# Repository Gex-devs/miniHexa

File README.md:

# Mini Hexa

Rework of Hiwonders mini hexa 

# Version 2.0 

<!-- SCHEMA STARTS HERE -->

<!-- SCHEMA ENDS HERE -->

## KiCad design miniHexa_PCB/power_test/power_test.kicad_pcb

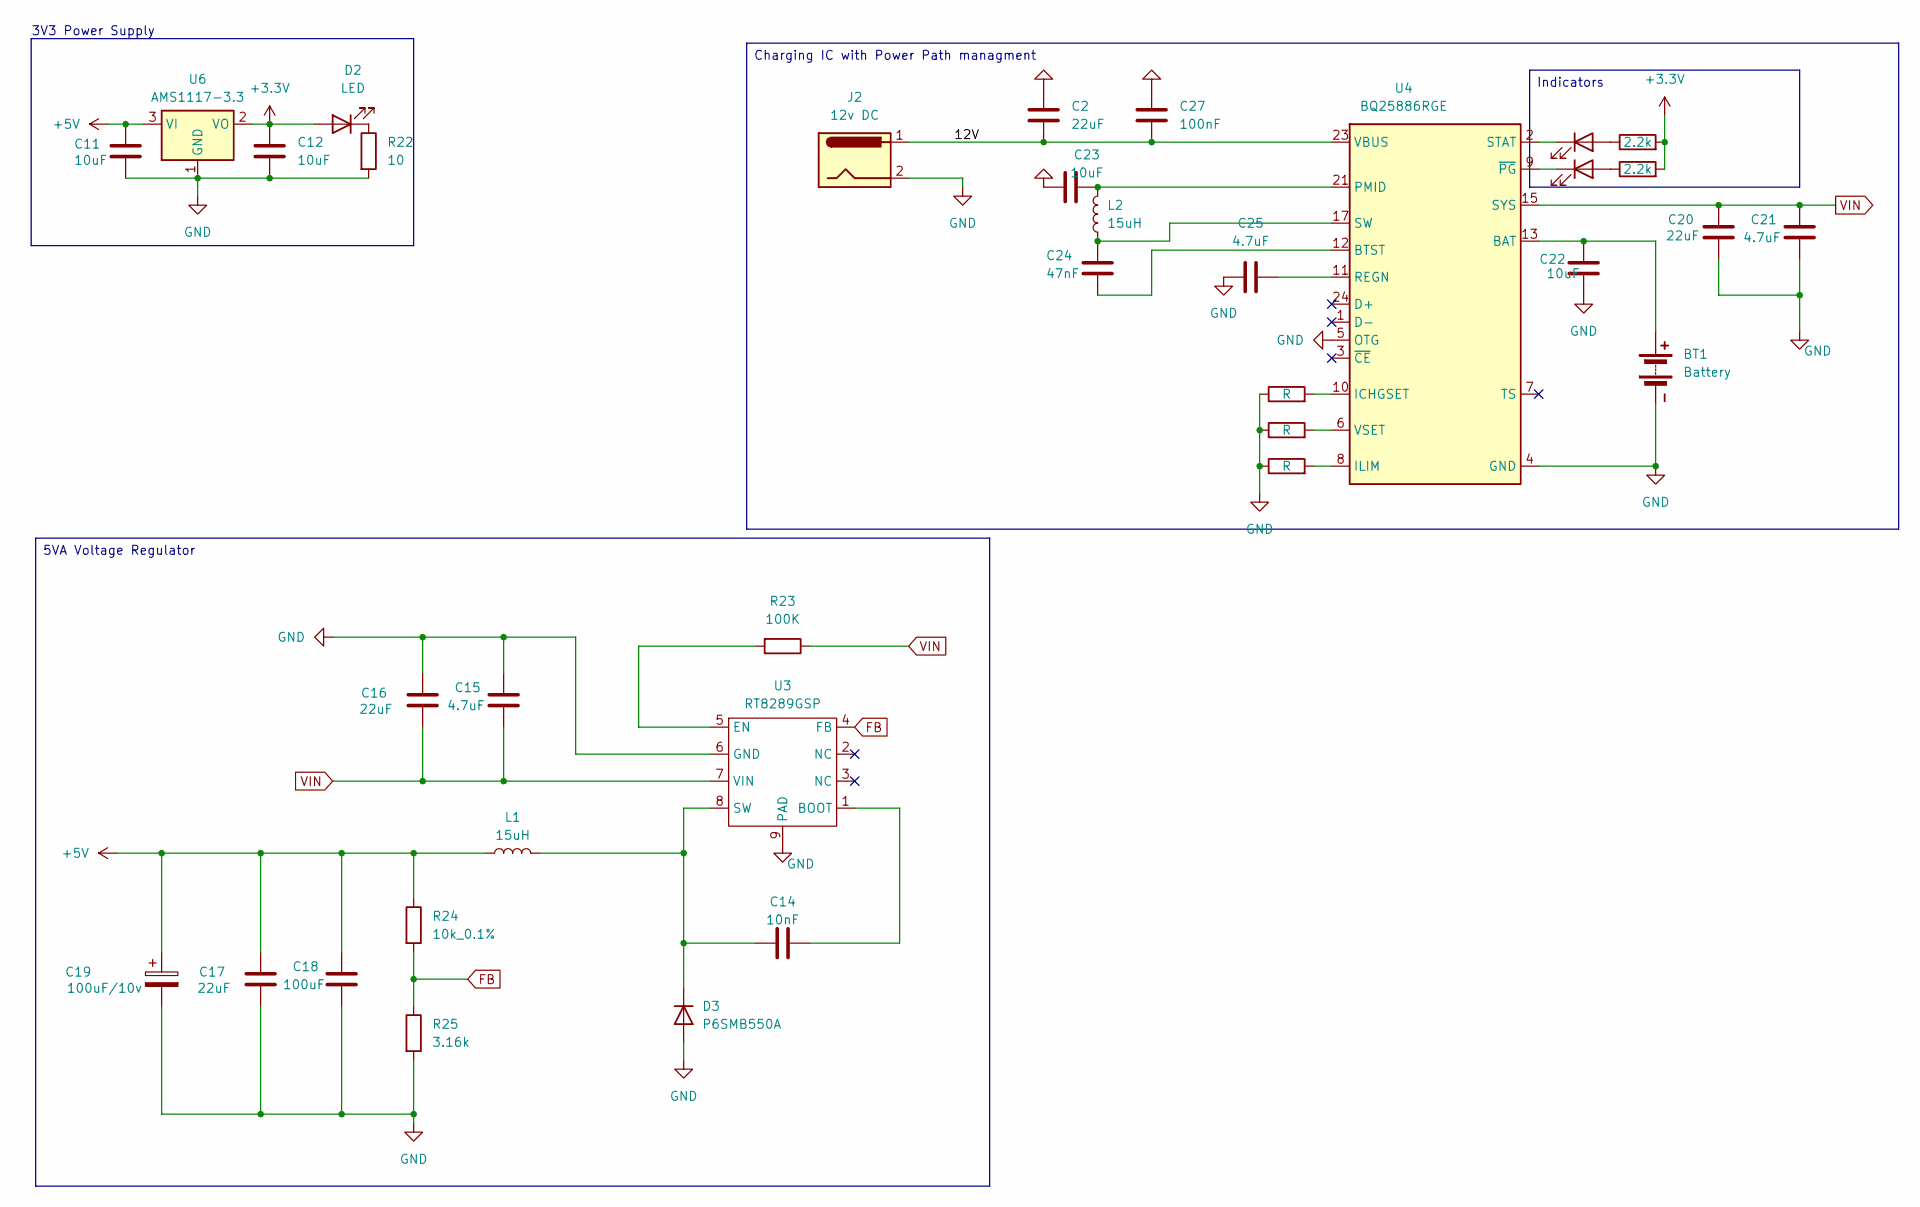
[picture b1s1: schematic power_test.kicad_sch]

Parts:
BT1: Battery; JST_XH_S2B-XH-A-1_1x02_P2.50mm_Horizontal
C2, C16, C17, C20: 22uF; C_0402_1005Metric
C11, C12, C22, C23: 10uF; C_0402_1005Metric
C14: 10nF; C_0402_1005Metric
C15, C21, C25: 4.7uF; C_0402_1005Metric
C18: 100uF; C_0402_1005Metric
C19: 100uF/10v; CP_Elec_5x5.4
C24: 47nF; C_0402_1005Metric
C27: 100nF; C_0402_1005Metric
D2, D4, D5: LED; LED_0805_2012Metric
D3: P6SMB550A; D_0805_2012Metric_Pad1.15x1.40mm_HandSolder
J2: 12v DC; BarrelJack_Wuerth_694102107102_1.0x3.9mm
L1, L2: 15uH; L_Panasonic_PCC-M0850M
R22: 10; R_0402_1005Metric
R23: 100K; R_0402_1005Metric
R24: 10k_0.1%; R_0402_1005Metric
R25: 3.16k; R_0402_1005Metric
R26, R30, R31: R; R_0402_1005Metric
R27, R28: 2.2k; R_0402_1005Metric
U3: RT8289GSP
U4: BQ25886RGE; Texas_RGE0024H_VQFN-24-1EP_4x4mm_P0.5mm_EP2.7x2.7mm
U6: AMS1117-3.3; SOT-223-3_TabPin2

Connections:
+3.3V: C12.1, D2.2 (A), R27.2, R28.2, U6.2 (VO)
+5V: C11.1, C17.2, C18.2, C19.1, L1.1, R24.1, U6.3 (VI)
/12V: C2.2, C27.2, J2.1, U4.23 (VBUS)
FB: R24.2, R25.1, U3.4 (FB)
GND: BT1.2 (GND), C2.1, C11.2, C12.2, C15.2, C16.2, C17.1, C18.1, C19.2, C20.1, C21.1, C22.2, C23.1, C25.1, C27.1, D3.2 (A), J2.2, R22.2, R25.2, R26.1, R30.1, R31.1, U3.6 (GND), U3.9 (PAD), U4.4 (GND), U4.5 (OTG), U4.19 (GND), U4.20 (GND), U4.25 (GND), U6.1 (GND)
unnamed: BT1.1 (+), C22.1, U4.13 (BAT), U4.14 (BAT)
unnamed: C23.2, L2.2, U4.21 (PMID), U4.22 (PMID)
unnamed: C24.1, L2.1, U4.17 (SW), U4.18 (SW)
unnamed: D2.1 (K), R22.1
unnamed: C14.1, D3.1 (K), L1.2, U3.8 (SW)
unnamed: D4.2 (A), R27.1
unnamed: D4.1 (K), U4.2 (STAT)
unnamed: D5.2 (A), R28.1
unnamed: D5.1 (K), U4.9 (~PG)
unnamed: C14.2, U3.1 (BOOT)
unnamed: R23.2, U3.5 (EN)
unnamed: C24.2, U4.12 (BTST)
unnamed: R26.2, U4.10 (ICHGSET)
unnamed: R31.2, U4.8 (ILIM)
unnamed: C25.2, U4.11 (REGN)
unnamed: R30.2, U4.6 (VSET)
VIN: C15.1, C16.1, C20.2, C21.2, R23.1, U3.7 (VIN), U4.15 (SYS), U4.16 (SYS)

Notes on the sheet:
3V3 Power Supply
5VA Voltage Regulator
Charging IC with Power Path managment
Indicators

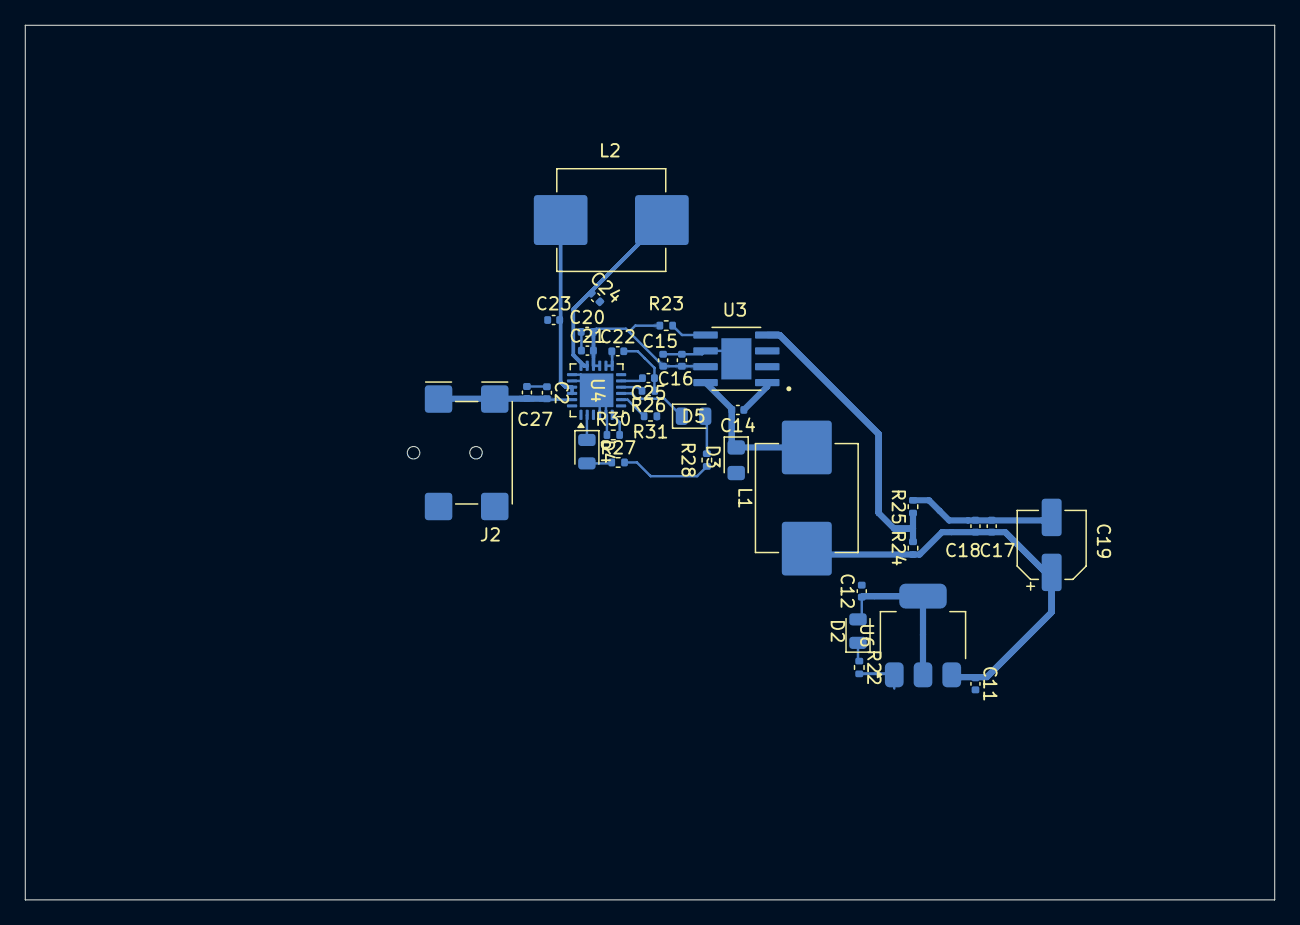
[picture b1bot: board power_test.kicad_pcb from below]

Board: 4 copper layers, 100.0 x 70.0 mm, 35 parts (35 on the bottom side), 22 nets.

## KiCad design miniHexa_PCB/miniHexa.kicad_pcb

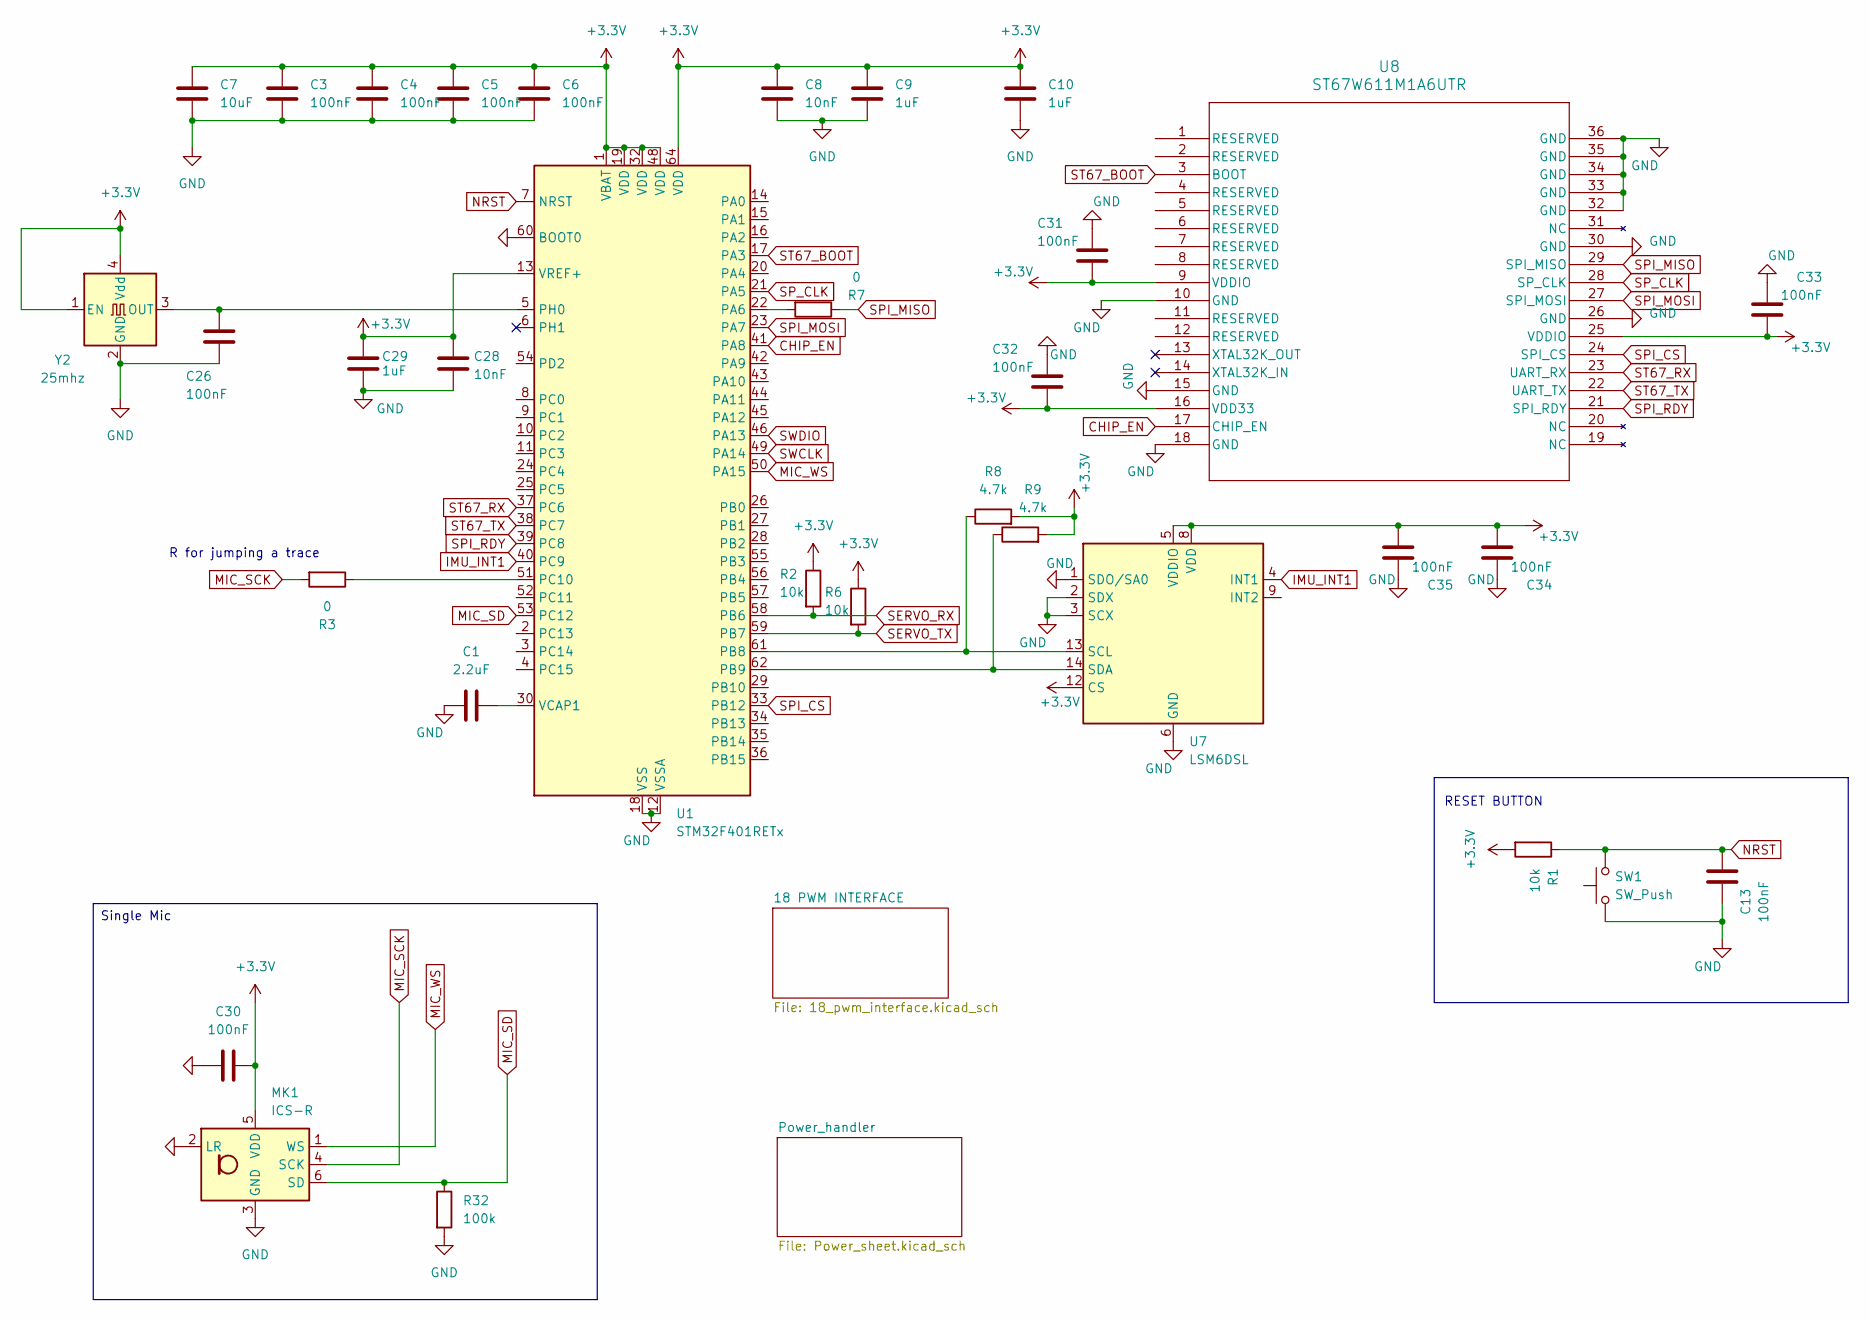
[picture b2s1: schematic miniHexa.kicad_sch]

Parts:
C1: 2.2uF; C_0402_1005Metric
C3, C4, C5, C6, C13, C26, C34, C35: 100nF; C_0402_1005Metric
C7: 10uF; C_0402_1005Metric
C8, C28: 10nF; C_0402_1005Metric
C9, C10, C29: 1uF; C_0402_1005Metric
C30, C31, C32, C33: 100nF; C_0805_2012Metric
MK1: ICS-R; InvenSense_ICS-43434-6_3.5x2.65mm
R1, R2, R6: 10k; R_0402_1005Metric
R3, R7: 0; R_0603_1608Metric
R8, R9: 4.7k; R_0402_1005Metric
R32: 100k; R_0402_1005Metric
SW1: SW_Push; SW_SPST_B3U-1000P
U1: STM32F401RETx; LQFP-64_10x10mm_P0.5mm
U7: LSM6DSL; LGA-14_3x2.5mm_P0.5mm_LayoutBorder3x4y
U8: ST67W611M1A6UTR; U_QFN32L_ST67W611M1_STM-L
Y2: 25mhz; Oscillator_SMD_Abracon_ASE-4Pin_3.2x2.5mm

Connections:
+3.3V: C3.1, C4.1, C5.1, C6.1, C7.1, C8.1, C9.1, C10.1, C28.1, C29.1, C30.2, C31.2, C32.2, C33.2, C34.2, C35.2, MK1.5 (VDD), R1.2, R2.1, R6.1, R8.2, R9.2, U1.1 (VBAT), U1.13 (VREF+), U1.19 (VDD), U1.32 (VDD), U1.48 (VDD), U1.64 (VDD), U7.5 (VDDIO), U7.8 (VDD), U7.12 (CS), U8.9 (VDDIO), U8.16 (VDD33), U8.25 (VDDIO), Y2.1 (EN), Y2.4 (Vdd); also elsewhere on the board
CHIP_EN: U1.41 (PA8), U8.17 (CHIP_EN)
GND: C1.1, C3.2, C4.2, C5.2, C6.2, C7.2, C8.2, C9.2, C10.2, C13.1, C26.2, C28.2, C29.2, C30.1, C31.1, C32.1, C33.1, C34.1, C35.1, MK1.2 (LR), MK1.3 (GND), R32.2, SW1.1, U1.12 (VSSA), U1.18 (VSS), U1.31 (VSS), U1.47 (VSS), U1.60 (BOOT0), U1.63 (VSS), U7.1 (SDO/SA0), U7.2 (SDX), U7.3 (SCX), U7.6 (GND), U7.7 (GND), U8.10 (GND), U8.15 (GND), U8.18 (GND), U8.26 (GND), U8.30 (GND), U8.32 (GND), U8.33 (GND), U8.34 (GND), U8.35 (GND), U8.36 (GND), Y2.2 (GND); also elsewhere on the board
IMU_INT1: U1.40 (PC9), U7.4 (INT1)
MIC_SCK: MK1.4 (SCK), R3.2
MIC_SD: MK1.6 (SD), R32.1, U1.53 (PC12)
MIC_WS: MK1.1 (WS), U1.50 (PA15)
NRST: C13.2, R1.1, SW1.2, U1.7 (NRST)
unnamed: R7.2, U1.22 (PA6)
unnamed: R8.1, U1.61 (PB8), U7.13 (SCL)
unnamed: R9.1, U1.62 (PB9), U7.14 (SDA)
unnamed: R3.1, U1.51 (PC10)
unnamed: C26.1, U1.5 (PH0), Y2.3 (OUT)
unnamed: C1.2, U1.30 (VCAP1)
SERVO_RX: R2.2, U1.58 (PB6); also elsewhere on the board
SERVO_TX: R6.2, U1.59 (PB7); also elsewhere on the board
SPI_CS: U1.33 (PB12), U8.24 (SPI_CS)
SPI_MISO: R7.1, U8.29 (SPI_MISO)
SPI_MOSI: U1.23 (PA7), U8.27 (SPI_MOSI)
SPI_RDY: U1.39 (PC8), U8.21 (SPI_RDY)
SP_CLK: U1.21 (PA5), U8.28 (SP_CLK)
ST67_BOOT: U1.17 (PA3), U8.3 (BOOT)
ST67_RX: U1.37 (PC6), U8.23 (UART_RX)
ST67_TX: U1.38 (PC7), U8.22 (UART_TX)
SWCLK: U1.49 (PA14)
SWDIO: U1.46 (PA13)

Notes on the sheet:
RESET BUTTON
R for jumping a trace
Single Mic

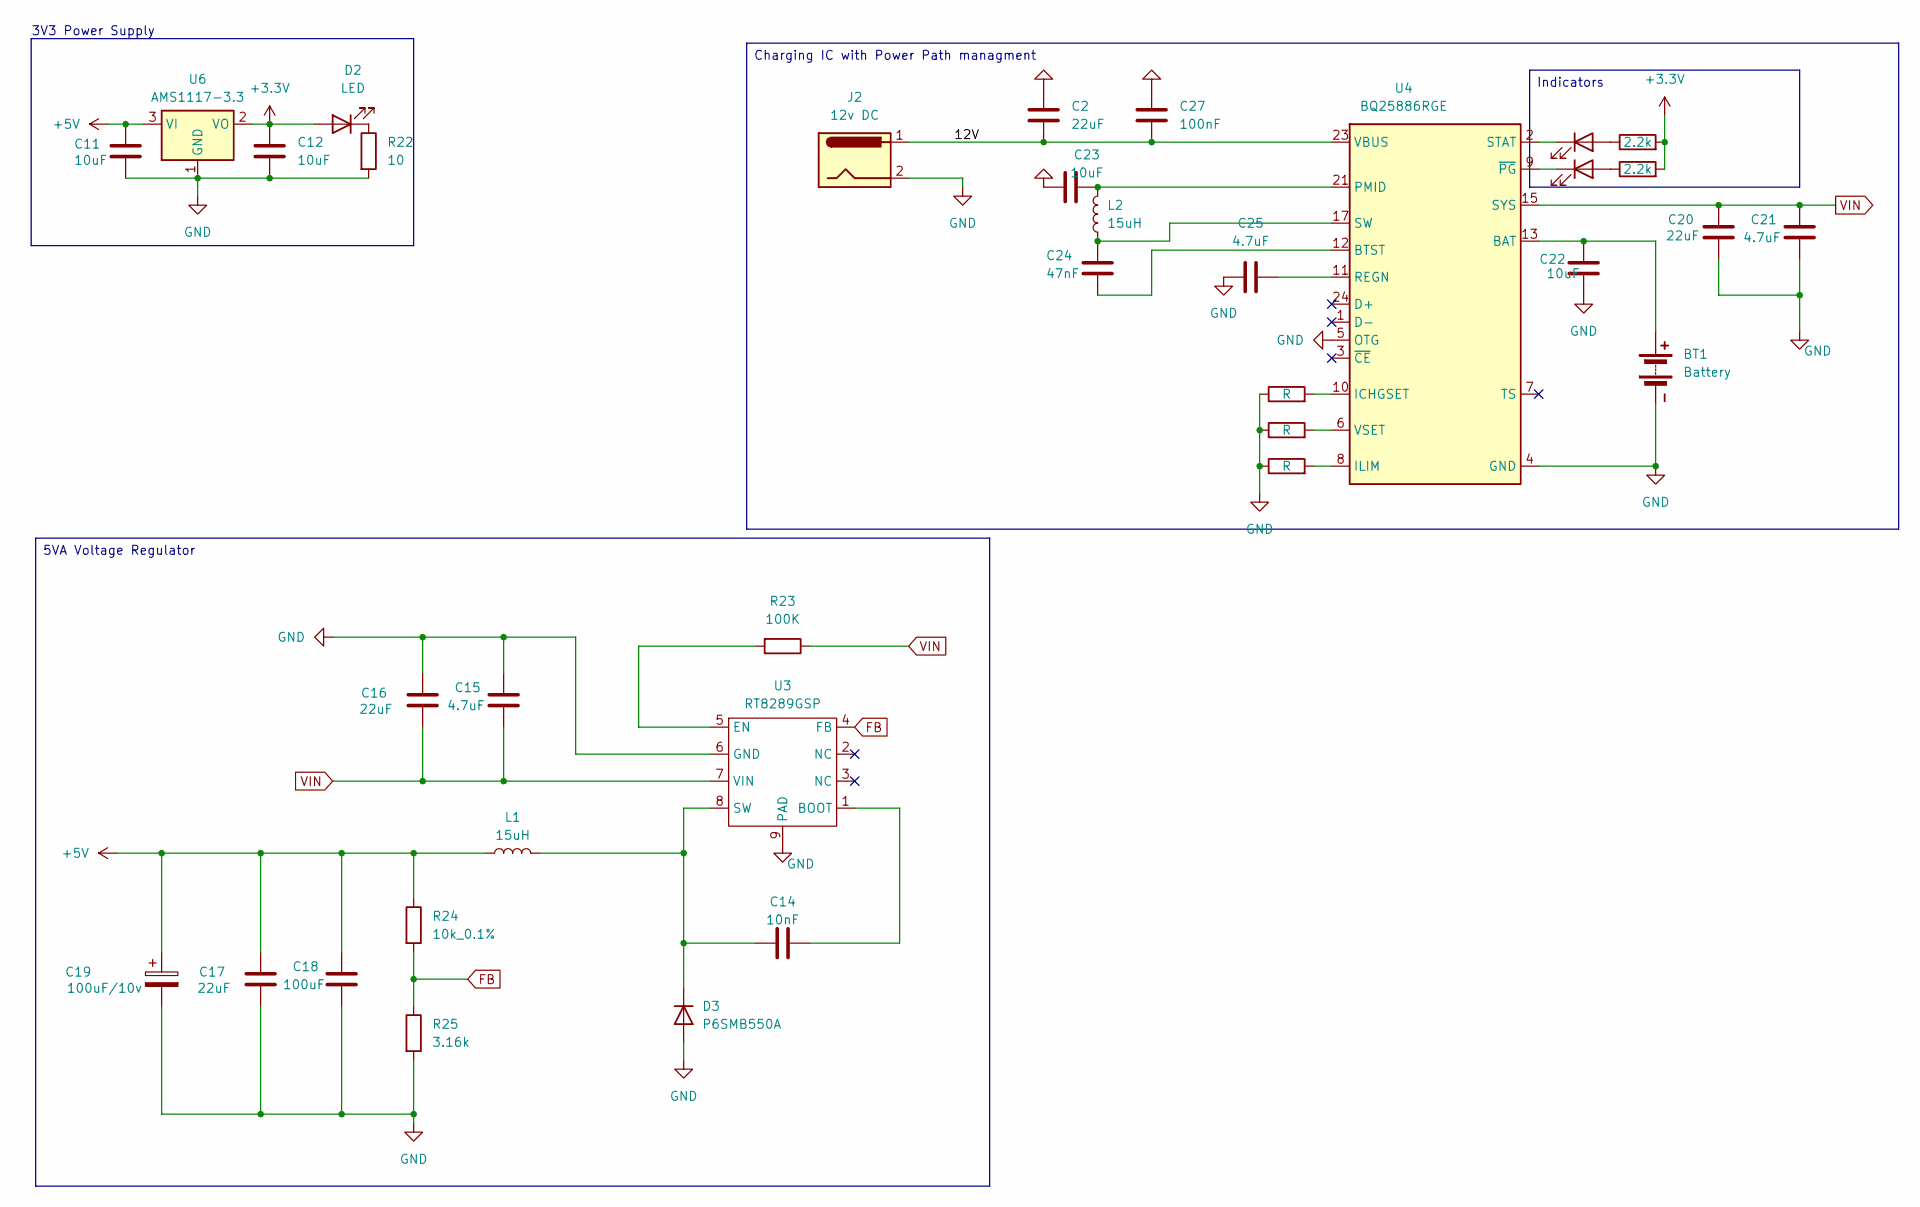
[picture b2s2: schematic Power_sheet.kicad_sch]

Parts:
BT1: Battery; JST_XH_S2B-XH-A-1_1x02_P2.50mm_Horizontal
C2, C16, C17, C20: 22uF; C_0402_1005Metric
C11, C12, C22, C23: 10uF; C_0402_1005Metric
C14: 10nF; C_0402_1005Metric
C15, C21, C25: 4.7uF; C_0402_1005Metric
C18: 100uF; C_0402_1005Metric
C19: 100uF/10v; CP_Elec_5x5.4
C24: 47nF; C_0402_1005Metric
C27: 100nF; C_0402_1005Metric
D2, D4, D5: LED; LED_0805_2012Metric
D3: P6SMB550A; D_0805_2012Metric_Pad1.15x1.40mm_HandSolder
J2: 12v DC; BarrelJack_Wuerth_694102107102_1.0x3.9mm
L1, L2: 15uH; L_Panasonic_PCC-M0850M
R22: 10; R_0402_1005Metric
R23: 100K; R_0402_1005Metric
R24: 10k_0.1%; R_0402_1005Metric
R25: 3.16k; R_0402_1005Metric
R26, R30, R31: R; R_0402_1005Metric
R27, R28: 2.2k; R_0402_1005Metric
U3: RT8289GSP
U4: BQ25886RGE; Texas_RGE0024H_VQFN-24-1EP_4x4mm_P0.5mm_EP2.7x2.7mm
U6: AMS1117-3.3; SOT-223-3_TabPin2

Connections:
+3.3V: C12.1, D2.2 (A), R27.2, R28.2, U6.2 (VO); also elsewhere on the board
+5V: C11.1, C17.2, C18.2, C19.1, L1.1, R24.1, U6.3 (VI); also elsewhere on the board
/Power_handler/12V: C2.2, C27.2, J2.1, U4.23 (VBUS)
FB: R24.2, R25.1, U3.4 (FB)
GND: BT1.2 (GND), C2.1, C11.2, C12.2, C15.2, C16.2, C17.1, C18.1, C19.2, C20.1, C21.1, C22.2, C23.1, C25.1, C27.1, D3.2 (A), J2.2, R22.2, R25.2, R26.1, R30.1, R31.1, U3.6 (GND), U3.9 (PAD), U4.4 (GND), U4.5 (OTG), U4.19 (GND), U4.20 (GND), U4.25 (GND), U6.1 (GND); also elsewhere on the board
unnamed: BT1.1 (+), C22.1, U4.13 (BAT), U4.14 (BAT)
unnamed: C23.2, L2.2, U4.21 (PMID), U4.22 (PMID)
unnamed: C24.1, L2.1, U4.17 (SW), U4.18 (SW)
unnamed: D2.1 (K), R22.1
unnamed: C14.1, D3.1 (K), L1.2, U3.8 (SW)
unnamed: D4.2 (A), R27.1
unnamed: D4.1 (K), U4.2 (STAT)
unnamed: D5.2 (A), R28.1
unnamed: D5.1 (K), U4.9 (~PG)
unnamed: C14.2, U3.1 (BOOT)
unnamed: R23.2, U3.5 (EN)
unnamed: C24.2, U4.12 (BTST)
unnamed: R26.2, U4.10 (ICHGSET)
unnamed: R31.2, U4.8 (ILIM)
unnamed: C25.2, U4.11 (REGN)
unnamed: R30.2, U4.6 (VSET)
VIN: C15.1, C16.1, C20.2, C21.2, R23.1, U3.7 (VIN), U4.15 (SYS), U4.16 (SYS)

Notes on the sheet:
3V3 Power Supply
Charging IC with Power Path managment
5VA Voltage Regulator
Indicators

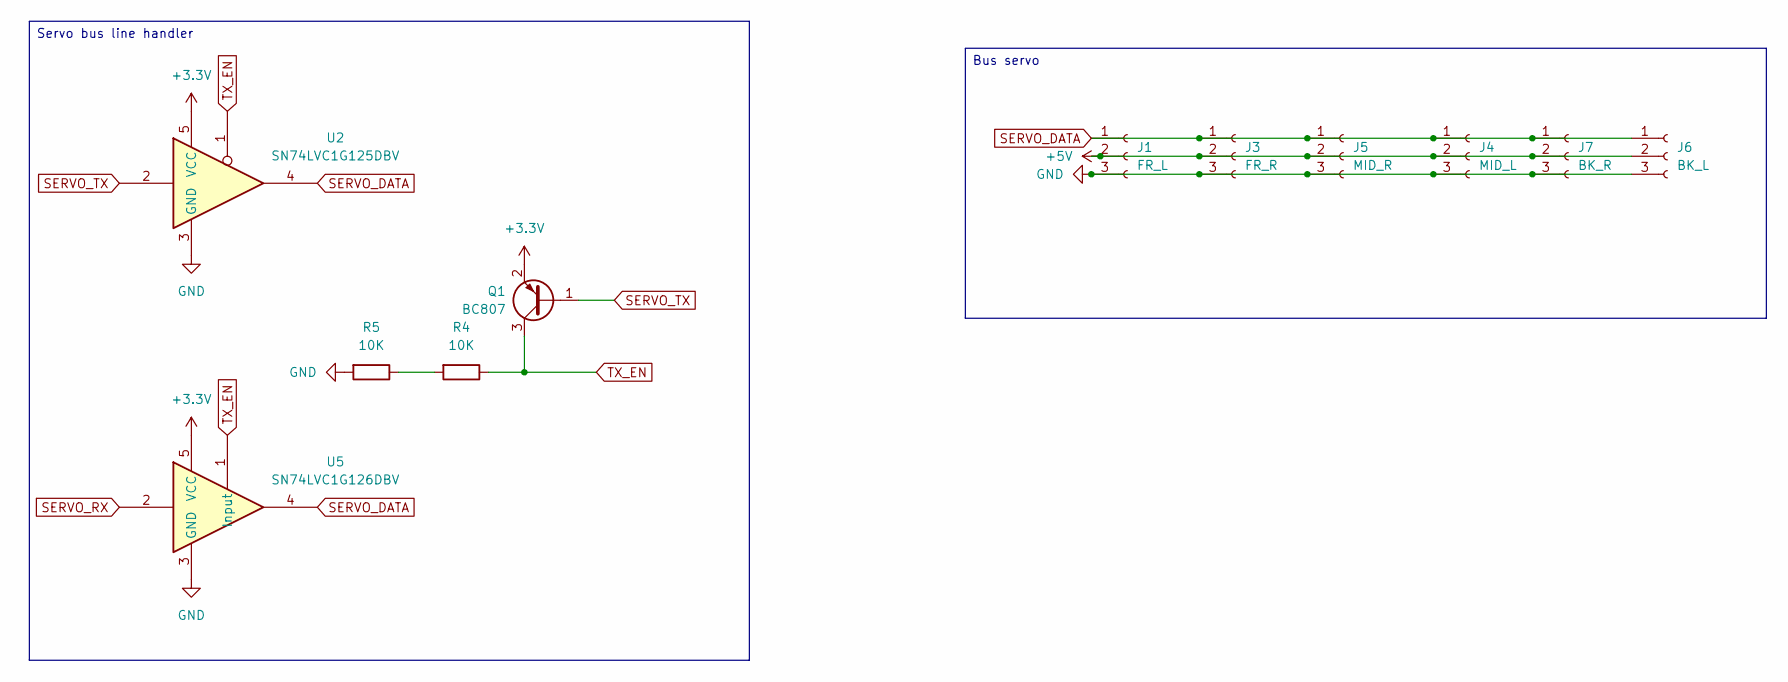
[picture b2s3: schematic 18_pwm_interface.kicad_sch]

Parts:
J1: FR_L; JST_XH_B3B-XH-A_1x03_P2.50mm_Vertical
J3: FR_R; JST_XH_B3B-XH-A_1x03_P2.50mm_Vertical
J4: MID_L; JST_XH_B3B-XH-A_1x03_P2.50mm_Vertical
J5: MID_R; JST_XH_B3B-XH-A_1x03_P2.50mm_Vertical
J6: BK_L; JST_XH_B3B-XH-A_1x03_P2.50mm_Vertical
J7: BK_R; JST_XH_B3B-XH-A_1x03_P2.50mm_Vertical
Q1: BC807; SOT-23
R4, R5: 10K; R_0402_1005Metric
U2: SN74LVC1G125DBV; SOT-23-5
U5: SN74LVC1G126DBV; SOT-23-5

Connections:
+3.3V: Q1.2 (E), U2.5 (VCC), U5.5 (VCC); also elsewhere on the board
+5V: J1.2, J3.2, J4.2, J5.2, J6.2, J7.2; also elsewhere on the board
GND: J1.3, J3.3, J4.3, J5.3, J6.3, J7.3, R5.2, U2.3 (GND), U5.3 (GND); also elsewhere on the board
unnamed: R4.2, R5.1
SERVO_DATA: J1.1, J3.1, J4.1, J5.1, J6.1, J7.1, U2.4, U5.4
SERVO_RX: U5.2; also elsewhere on the board
SERVO_TX: Q1.1 (B), U2.2; also elsewhere on the board
TX_EN: Q1.3 (C), R4.1, U2.1, U5.1 (Input)

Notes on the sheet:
Bus servo
Servo bus line handler

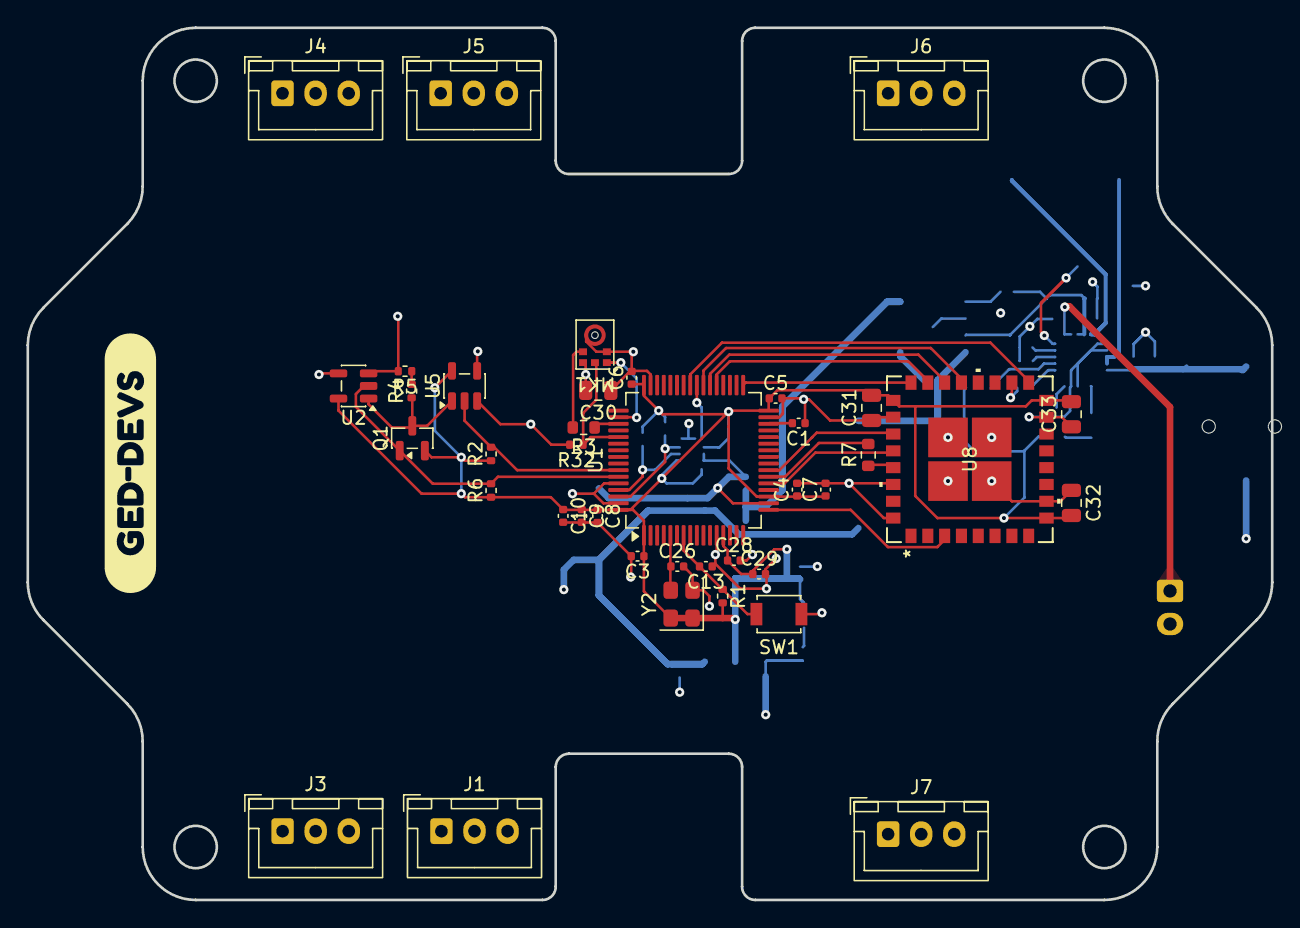
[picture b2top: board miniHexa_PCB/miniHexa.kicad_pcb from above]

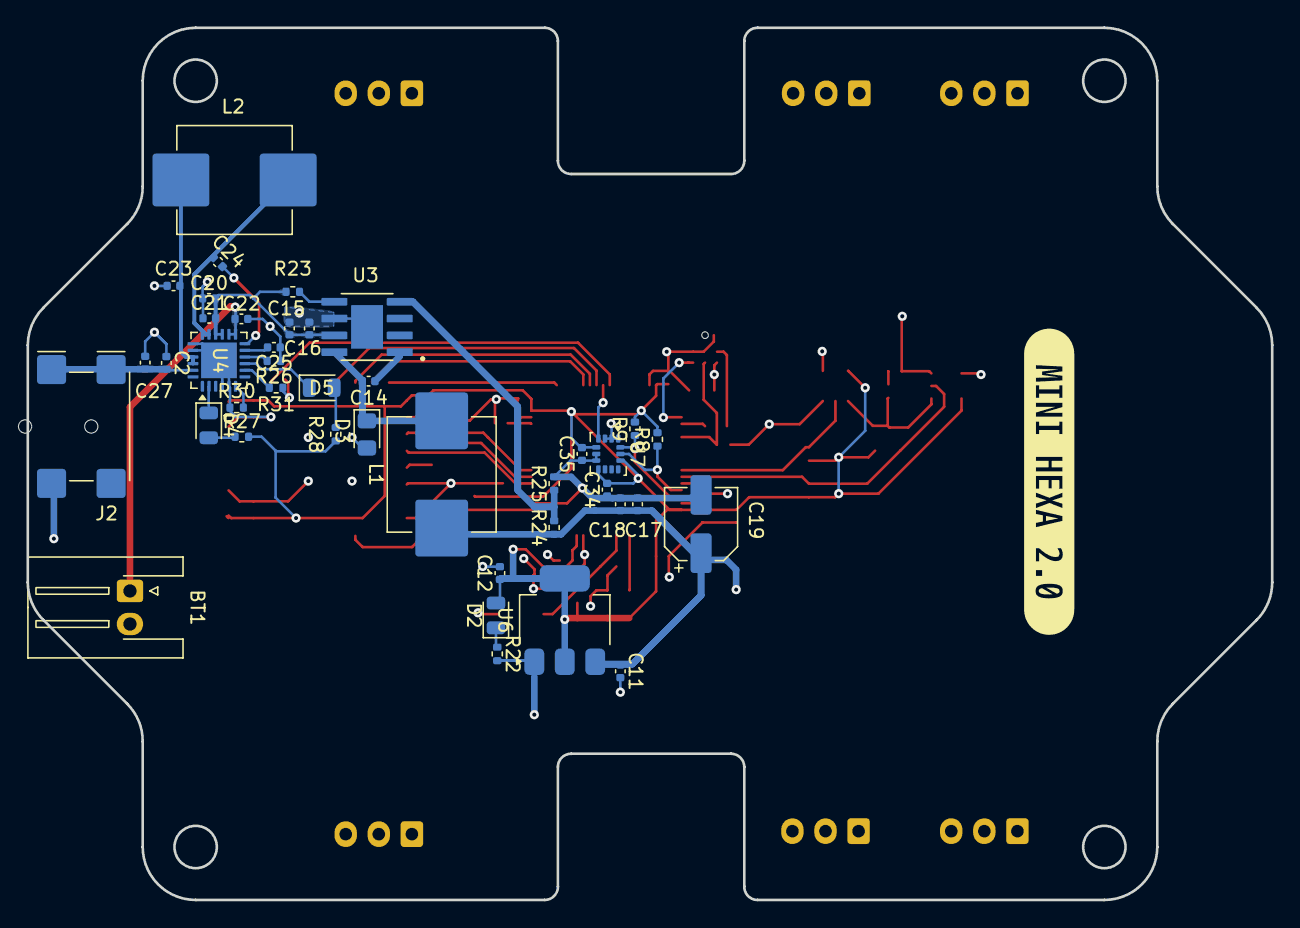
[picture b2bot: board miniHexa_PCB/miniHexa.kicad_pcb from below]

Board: 4 copper layers, 94.0 x 65.9 mm, 82 parts (42 on the bottom side), 47 nets.

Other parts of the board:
kibuzzard-6A883BEF: G***; kibuzzard-6A883BEF
kibuzzard-6AB37117: G***; kibuzzard-6AB37117

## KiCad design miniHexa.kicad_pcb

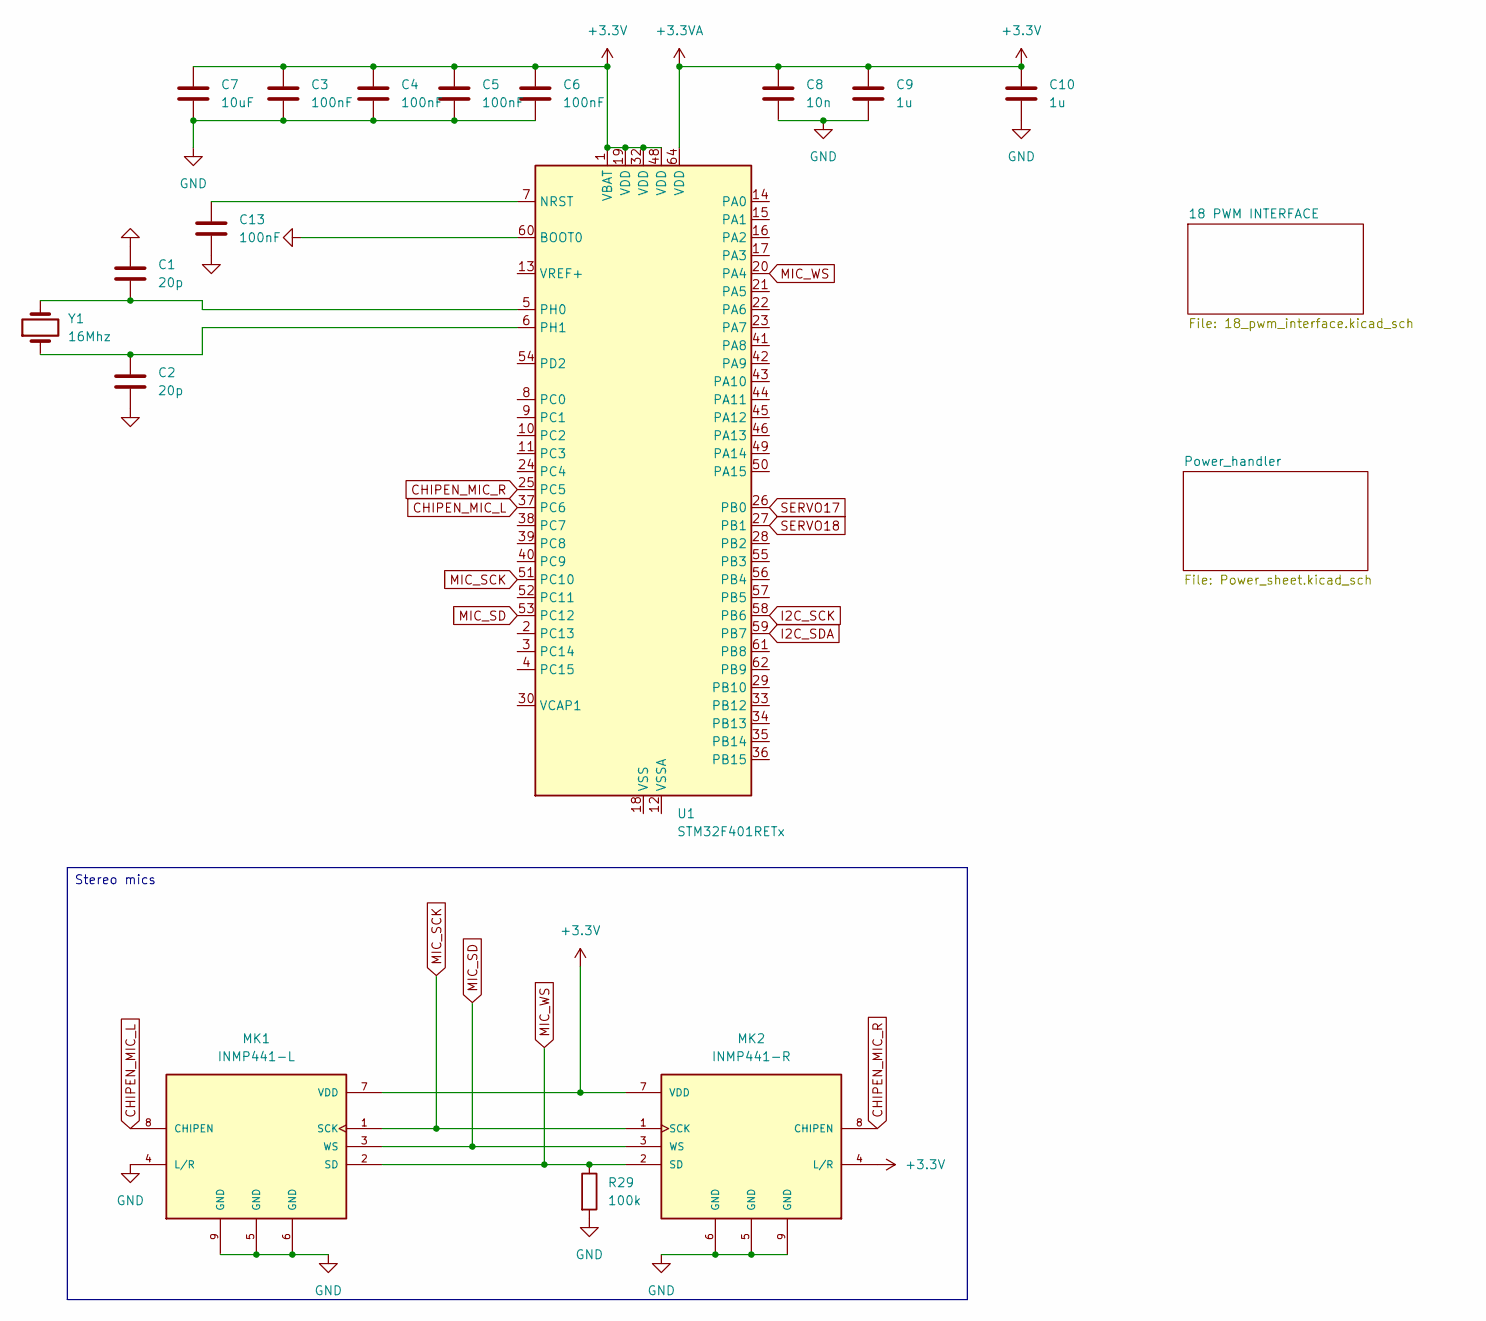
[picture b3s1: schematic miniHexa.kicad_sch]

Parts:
C1, C2: 20p; C_0805_2012Metric
C3, C4, C5, C6, C13: 100nF; C_0805_2012Metric
C7: 10uF; C_0805_2012Metric
C8: 10n; C_0805_2012Metric
C9, C10: 1u; C_0805_2012Metric
MK1: INMP441-L; MIC_INMP441ACEZ-R7; PARTREV 1.1
MK2: INMP441-R; MIC_INMP441ACEZ-R7; PARTREV 1.1
R29: 100k; R_0805_2012Metric
U1: STM32F401RETx; LQFP-64_10x10mm_P0.5mm
Y1: 16Mhz; Crystal_HC49-4H_Vertical

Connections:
+3.3V: C3.1, C4.1, C5.1, C6.1, C7.1, C8.1, C9.1, C10.1, MK1.7 (VDD), MK2.4 (L/R), MK2.7 (VDD), U1.1 (VBAT), U1.19 (VDD), U1.32 (VDD), U1.48 (VDD), U1.64 (VDD); also elsewhere on the board
CHIPEN_MIC_L: MK1.8 (CHIPEN), U1.37 (PC6); also elsewhere on the board
CHIPEN_MIC_R: MK2.8 (CHIPEN), U1.25 (PC5); also elsewhere on the board
GND: C1.1, C2.2, C3.2, C4.2, C5.2, C6.2, C7.2, C8.2, C9.2, C10.2, C13.2, MK1.4 (L/R), MK1.5 (GND), MK1.6 (GND), MK1.9 (GND), MK2.5 (GND), MK2.6 (GND), MK2.9 (GND), R29.2, U1.60 (BOOT0); also elsewhere on the board
I2C_SCK: U1.58 (PB6); also elsewhere on the board
I2C_SDA: U1.59 (PB7); also elsewhere on the board
MIC_SCK: MK1.1 (SCK), MK2.1 (SCK), U1.51 (PC10); also elsewhere on the board
MIC_SD: MK1.3 (WS), MK2.3 (WS), U1.53 (PC12); also elsewhere on the board
MIC_WS: MK1.2 (SD), MK2.2 (SD), R29.1, U1.20 (PA4); also elsewhere on the board
unnamed: C13.1, U1.7 (NRST)
unnamed: C1.2, U1.5 (PH0), Y1.2
unnamed: C2.1, U1.6 (PH1), Y1.1
unnamed: U1.18 (VSS), U1.31 (VSS), U1.47 (VSS), U1.63 (VSS)
SERVO17: U1.26 (PB0); also elsewhere on the board
SERVO18: U1.27 (PB1); also elsewhere on the board

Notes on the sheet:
Stereo mics
